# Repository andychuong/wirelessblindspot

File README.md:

# Wireless Blindspot Detection System

This project was designed to be an easy to install/use blindspot detection system for motor vehicles. It was inspired by the advances of technology and computed embedded into modern cars. 

This project is comprised of two unites, a receiver and a sensor. The sensor unit is attached to your rear quarter panel with a magnet and has an ultrasonic sensor attached to it. The receiver component is made to sit inside of your car with an array of LED lights to notify the driver of objects in their blindspot. 

## Technology
- Arduino
- Bluetooth
- Eagle CAD

## Hardware
- [2x SparkFun ProMicro 5v](https://www.sparkfun.com/products/12640)
- [2x xBee](https://www.sparkfun.com/products/8665)
- [Weatherproof Ultrasonic Sensor](https://www.amazon.com/Waterproof-Ultrasonic-Distance-Measuring-Transducer/dp/B01J5KZU8M)
- [Individually Addressable LED Strip](https://www.amazon.com/ALITOVE-WS2812B-Individually-Addressable-Waterproof/dp/B00ZHB9M6A)

## Images
More images [here](https://github.com/andychuong/wirelessblindspot/tree/master/Images)

## Going Futher
### Built in charging solution
Currently, this project has you remove the LiPo batteries and plug them in a charger when they are out of charge. In the future, it would be nice to implement some kind of integrated setup to allow users to charge the batteries without disassembling the units. 
### Weather Proofing
The sensor unit that is attached to the exterious of the vehicle would need to have some sort of weatherproofing added to it. The addition of some sort of gaskets would greatly improve this. 
### Size Reduction
The footprint of our units isn't overly large, however I believe the size can be greatly reduced. To improve this, my first though would be to use a microcontroller such as the Adafruit Feather Bluefruit. This would combine our microcontroller with our bluetooth units. This would also solve our charging situation. Another idea would be to completely build our own circuit boards with everything we need implemented into the PCB with surface mounted components. 

---
###### Done in collaboration with Sean Connolly, Elijah Fisk, and Alex Schwartz.

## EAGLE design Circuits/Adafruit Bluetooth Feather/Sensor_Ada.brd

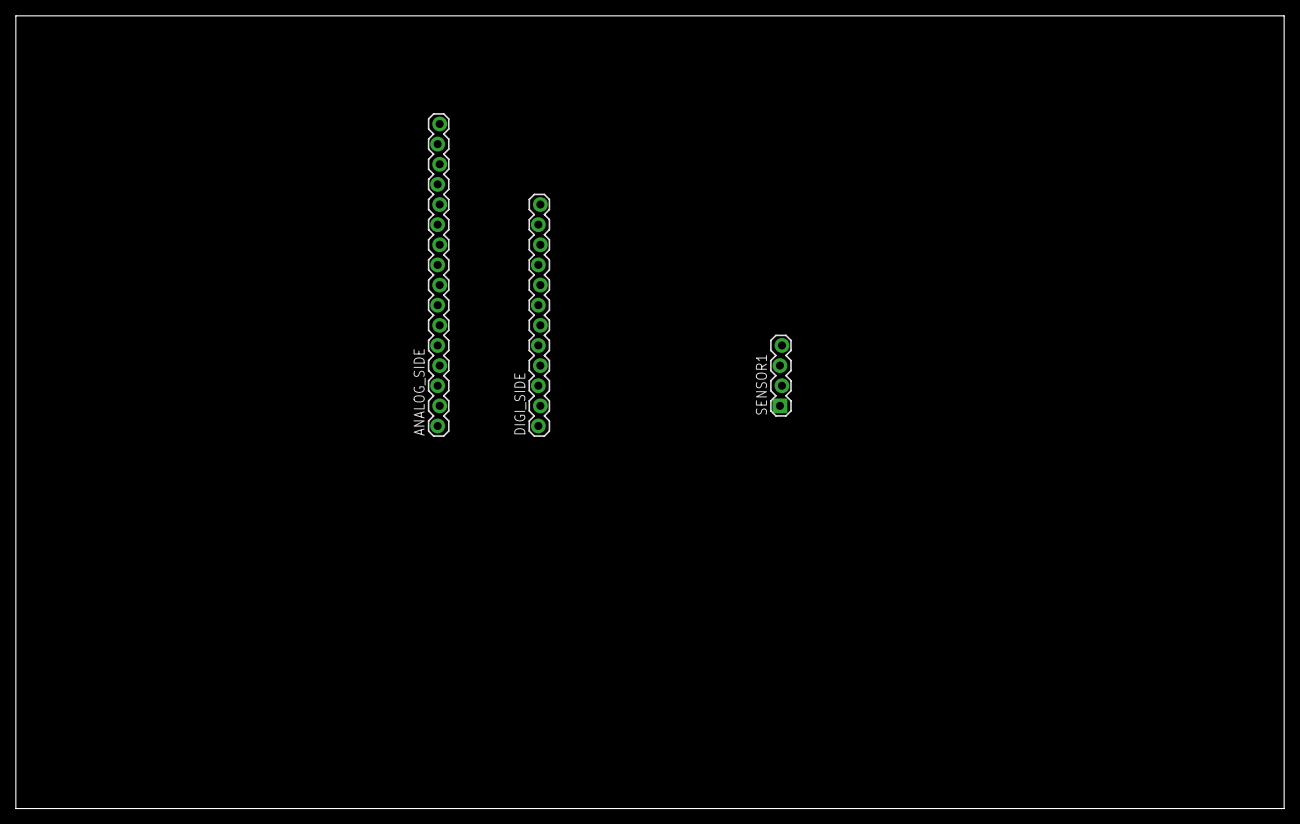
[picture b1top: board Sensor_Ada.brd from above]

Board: 2 copper layers, 160.0 x 100.0 mm, 3 parts (0 on the bottom side), 3 nets, no tracks yet.

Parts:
ANALOG_SIDE: 1X16_LOCK
DIGI_SIDE: 1X12_LOCK
SENSOR1: 1X04_LOCK

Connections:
ECHO: DIGI_SIDE.1, SENSOR1.2
GND: ANALOG_SIDE.13, SENSOR1.1
TRIG: DIGI_SIDE.2, SENSOR1.3

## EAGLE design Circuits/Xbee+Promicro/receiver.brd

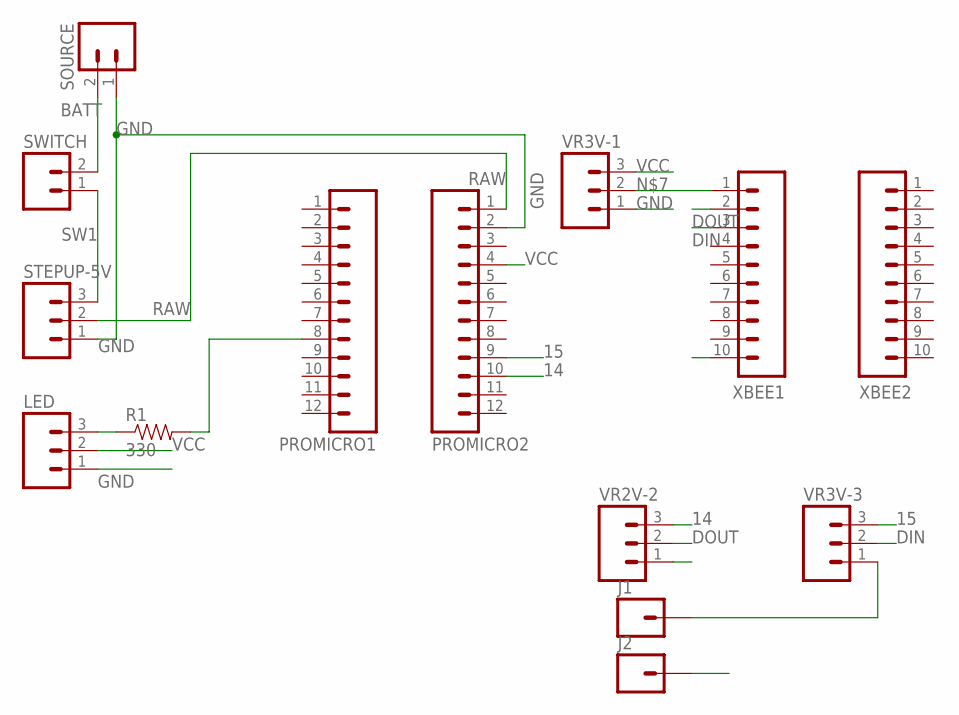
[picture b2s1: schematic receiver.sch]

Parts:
J1, J2: M01PTH; 1X01
LED: M03LOCK; 1X03_LOCK
PROMICRO1, PROMICRO2: M12LOCK; 1X12_LOCK
R1: 330; AXIAL-0.4
SOURCE: M02JST-PTH-VERT; JST-2-PTH-VERT
STEPUP-5V: M03LOCK; 1X03_LOCK
SWITCH: M02LOCK; 1X02_LOCK
VR2V-2, VR3V-1, VR3V-3: M03LOCK; 1X03_LOCK
XBEE1, XBEE2: M10LOCK; 1X10_LOCK

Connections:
14: PROMICRO2.10, VR2V-2.3
15: PROMICRO2.9, VR3V-3.3
BATT: SOURCE.2, SWITCH.2
DIN: VR3V-3.2, XBEE1.3
DOUT: VR2V-2.2, XBEE1.2
GND: J1.1, J2.1, LED.1, PROMICRO2.2, SOURCE.1, STEPUP-5V.1, VR2V-2.1, VR3V-1.1, VR3V-3.1
unnamed: LED.3, R1.P$1 (1)
unnamed: PROMICRO1.8, R1.P$2 (2)
unnamed: VR3V-1.2, XBEE1.1
RAW: PROMICRO2.1, STEPUP-5V.2
SW1: STEPUP-5V.3, SWITCH.1
VCC: LED.2, PROMICRO2.4, VR3V-1.3

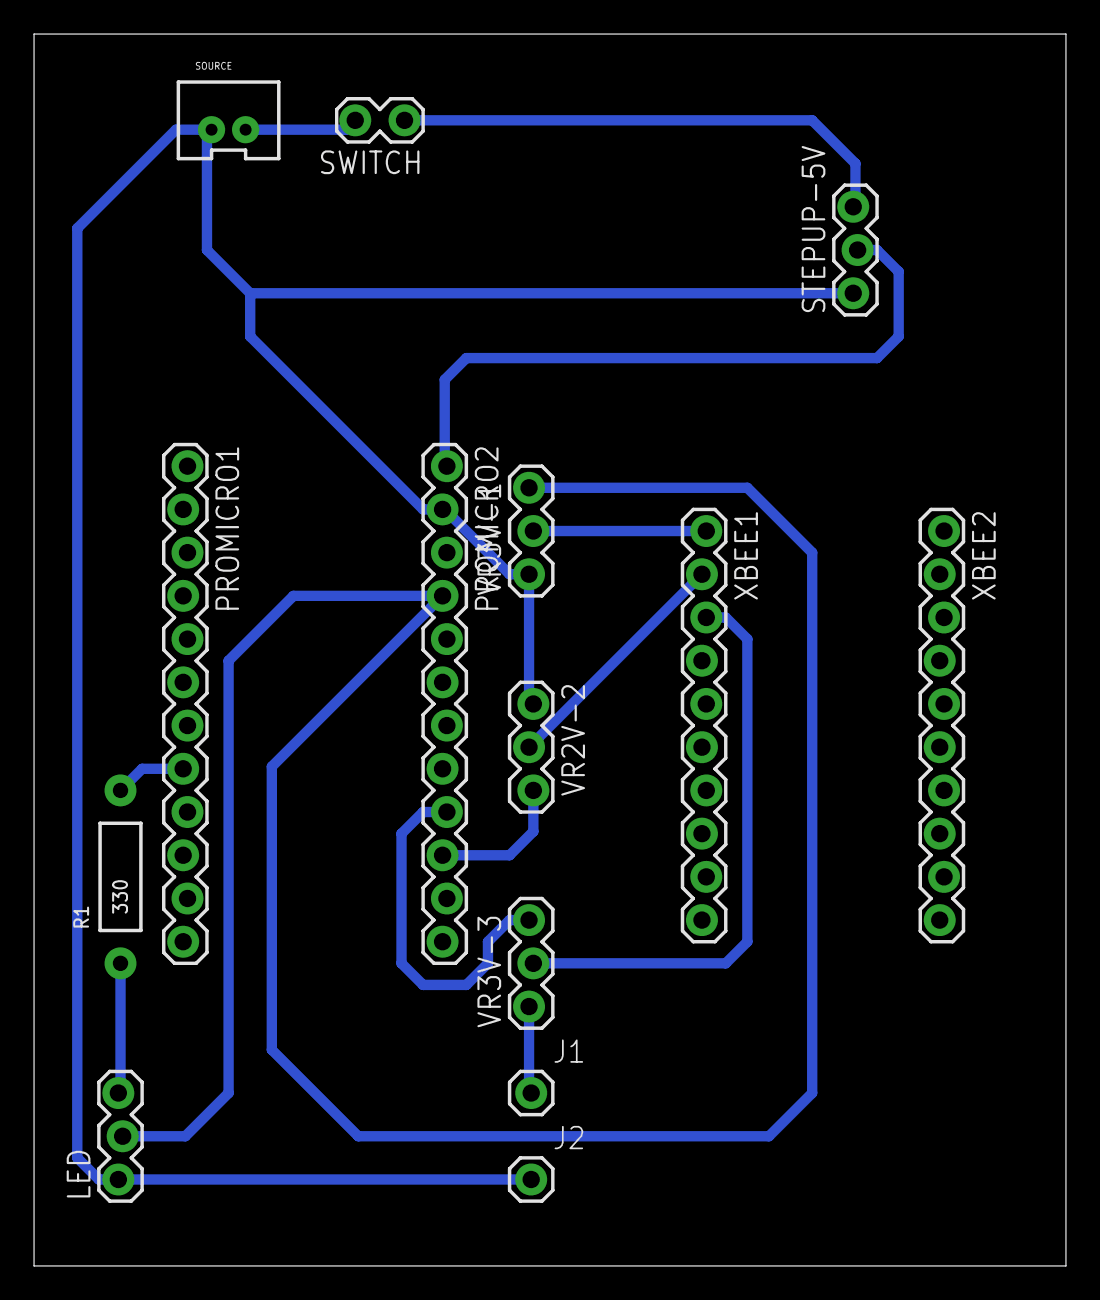
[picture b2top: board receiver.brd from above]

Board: 2 copper layers, 60.6 x 72.4 mm, 14 parts (0 on the bottom side), 12 nets.

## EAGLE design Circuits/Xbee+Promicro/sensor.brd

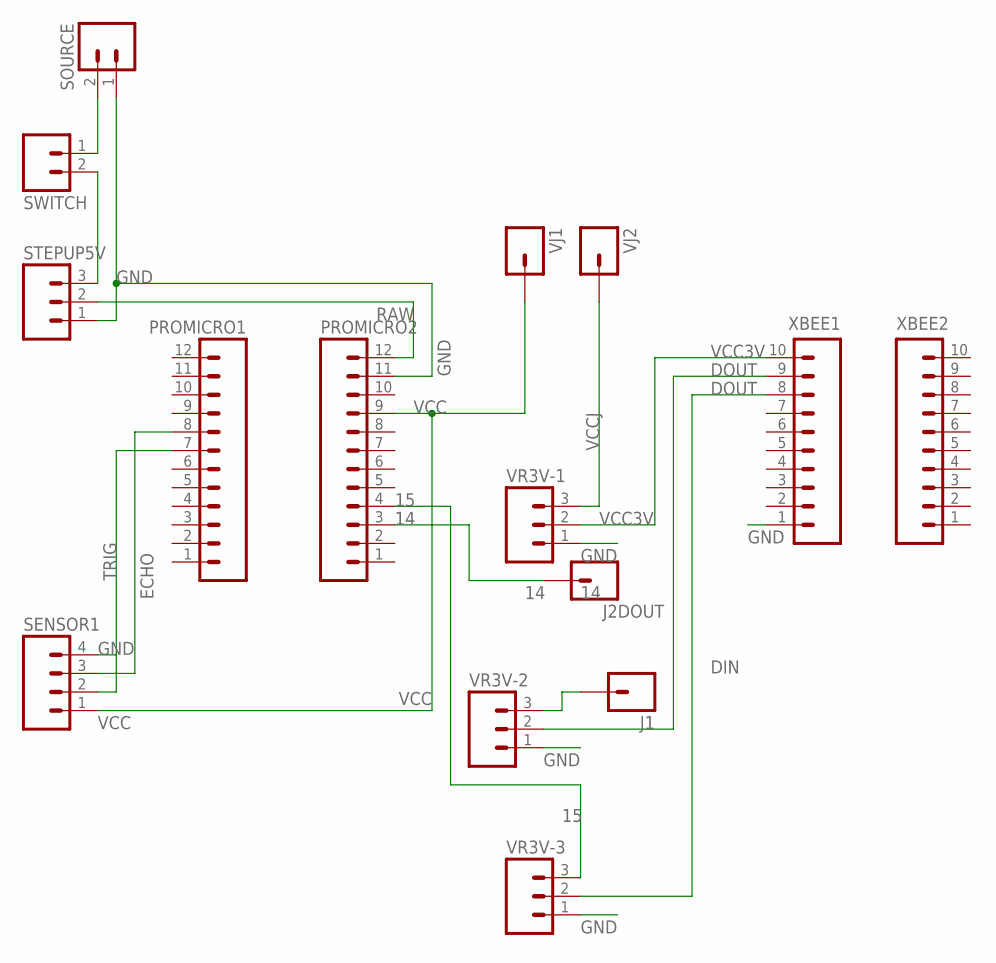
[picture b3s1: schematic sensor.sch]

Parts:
J1, J2: M01PTH; 1X01
PROMICRO1, PROMICRO2: M12LOCK; 1X12_LOCK
SENSOR1: M04LOCK; 1X04_LOCK
SOURCE: M02JST-PTH-VERT; JST-2-PTH-VERT
STEPUP5V: M03PTH; 1X03
SWITCH: M02PTH; 1X02
VJ1, VJ2: M01PTH; 1X01
VR3V-1, VR3V-2, VR3V-3: M03PTH; 1X03
XBEE1, XBEE2: M10LOCK; 1X10_LOCK

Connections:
14: J2.1, PROMICRO2.3
15: PROMICRO2.4, VR3V-3.3
DIN: VR3V-3.2, XBEE1.8
DOUT: VR3V-2.2, XBEE1.9
ECHO: PROMICRO1.8, SENSOR1.3
GND: PROMICRO2.11, SENSOR1.4, SOURCE.1, STEPUP5V.1, VR3V-1.1, VR3V-2.1, VR3V-3.1, XBEE1.1
unnamed: SOURCE.2, SWITCH.1
unnamed: STEPUP5V.3, SWITCH.2
unnamed: J1.1, VR3V-2.3
RAW: PROMICRO2.12, STEPUP5V.2
TRIG: PROMICRO1.7, SENSOR1.2
VCC: PROMICRO2.9, SENSOR1.1, VJ1.1
VCC3V: VR3V-1.2, XBEE1.10
VCCJ: VJ2.1, VR3V-1.3

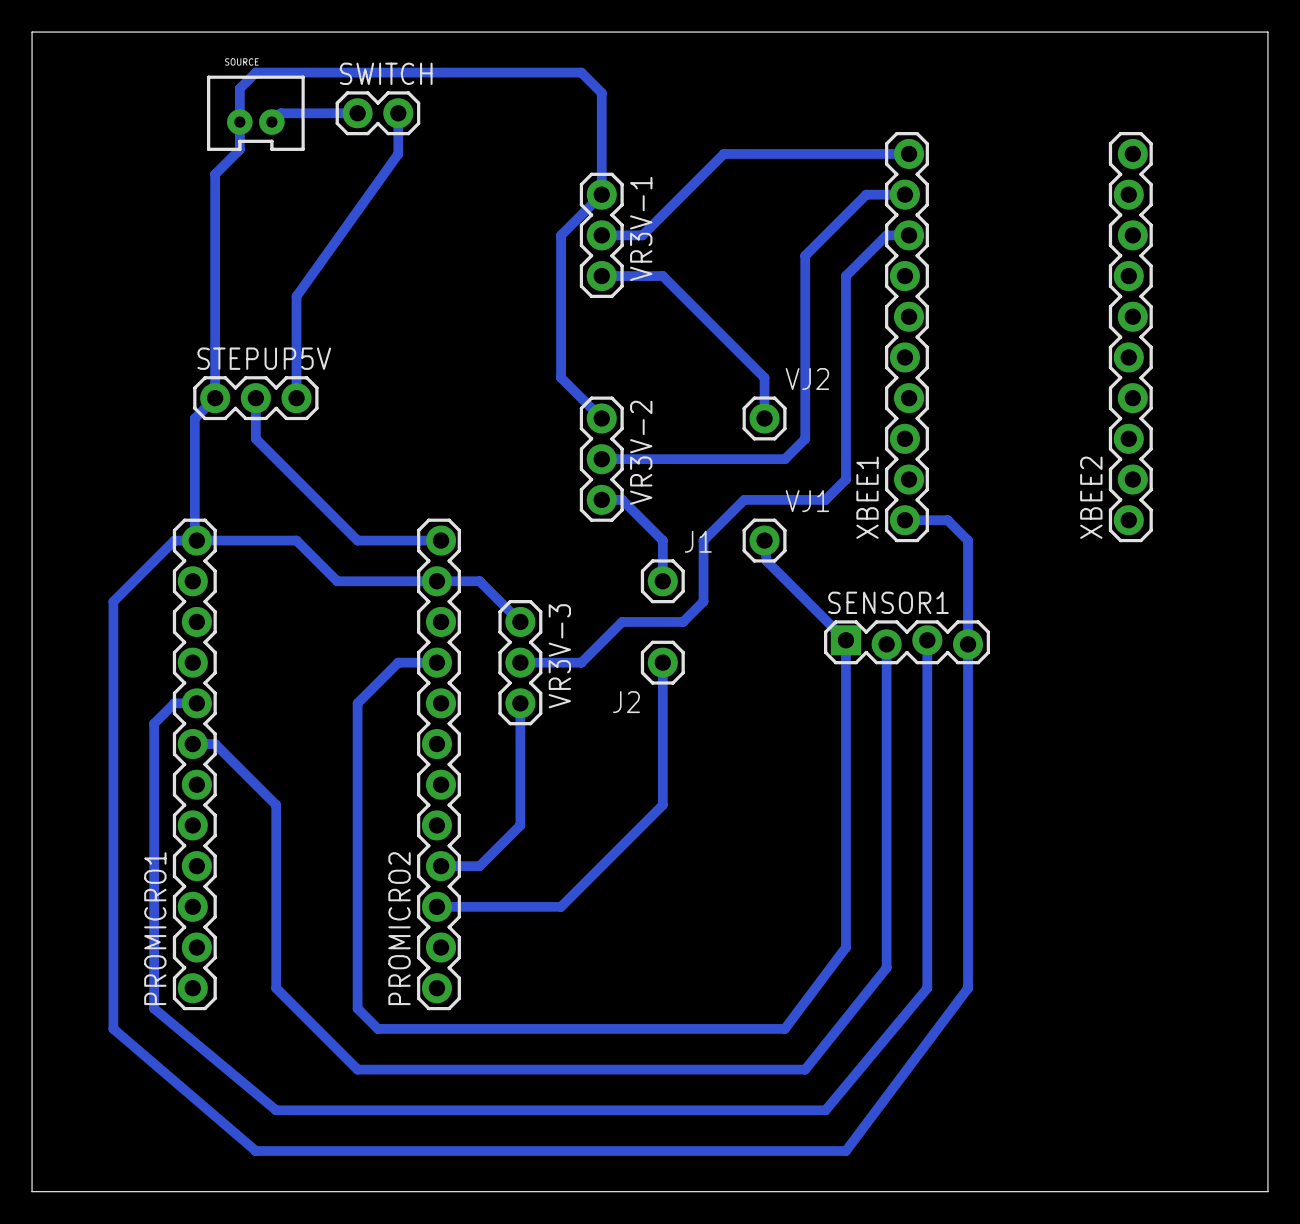
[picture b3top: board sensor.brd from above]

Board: 2 copper layers, 77.1 x 72.4 mm, 15 parts (0 on the bottom side), 14 nets.

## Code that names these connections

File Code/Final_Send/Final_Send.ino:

#include <SoftwareSerial.h>
// XBee's DOUT (TX) is connected to pin 14 (Arduino's Software RX)
// XBee's DIN (RX) is connected to pin 15 (Arduino's Software TX)
SoftwareSerial XBee(14, 15); // RX, TX
// ---------------------------------------------------------------------------
// Example NewPing library sketch that does a ping about 20 times per second.
// ---------------------------------------------------------------------------
#include <NewPing.h>

#define TRIGGER_PIN  3  // RX Arduino pin tied to trigger pin on the ultrasonic sensor.
#define ECHO_PIN     2  // TX Arduino pin tied to echo pin on the ultrasonic sensor.
#define MAX_DISTANCE 450 // Maximum distance we want to ping for (in centimeters). Maximum sensor distance is rated at 400-500cm.

NewPing sonar(TRIGGER_PIN, ECHO_PIN, MAX_DISTANCE); // NewPing setup of pins and maximum distance.
void setup() {
  Serial.begin(9600); // Open serial monitor at 115200 baud to see ping results.
  //pinMode(LEDPin, OUTPUT);
  XBee.begin(9600);
}

void loop() {
  delay(50);                      // Wait 50ms between pings (about 20 pings/sec). 29ms should be the shortest delay between pings.
  unsigned int uS = sonar.ping_median(); // Returning median pings at a rate of 3Hz.
  int distance = uS / US_ROUNDTRIP_CM;
  if (distance < 5){
    distance=500;
  }
  
  XBee.write(distance);
 // Serial.print("Ping: ");
  Serial.println(distance); // Convert ping time to distance and print result (0 = outside set distance range, no ping echo)
}

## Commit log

2018-02-23 Version 1 Prototyping
2018-02-28 Adafruit featherboard prototypes
2018-11-06 images
2018-11-07 sensor pcb drawing
2018-11-07 gitignore

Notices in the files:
parts and their libraries:
SparkFun-Connectors: Licensing: Creative Commons ShareAlike 4.0 International - https://creativecommons.org/licenses/by-sa/4.0
